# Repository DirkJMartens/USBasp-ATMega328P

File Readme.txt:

My implementation of the USBasp programmer on Windows 10 on a perfboard. 
Changes from the original include: 
  1. using an ATMega328P instead of the original ATMega44/88. 
  2. Changing the input circuit  from using zener diodes to regular diodes 
  3. Omitting the jumper bridges for "Self-programming" and "Slow CLK" 
  4. Power to target is always on. 
Software is using the libusbk driver (signed by Protostack Pty Ltd) and installed using Zadig. 

See project description file for full details.

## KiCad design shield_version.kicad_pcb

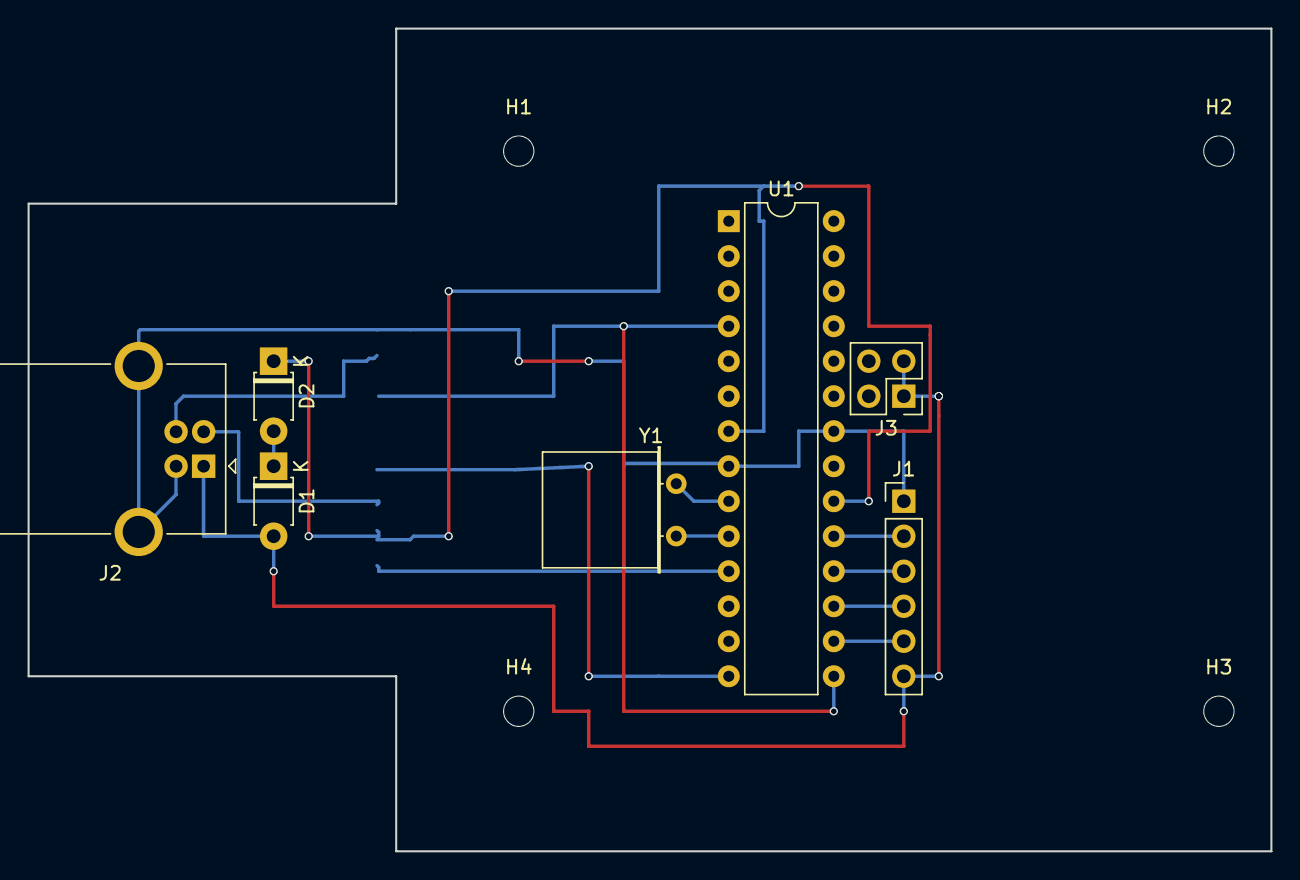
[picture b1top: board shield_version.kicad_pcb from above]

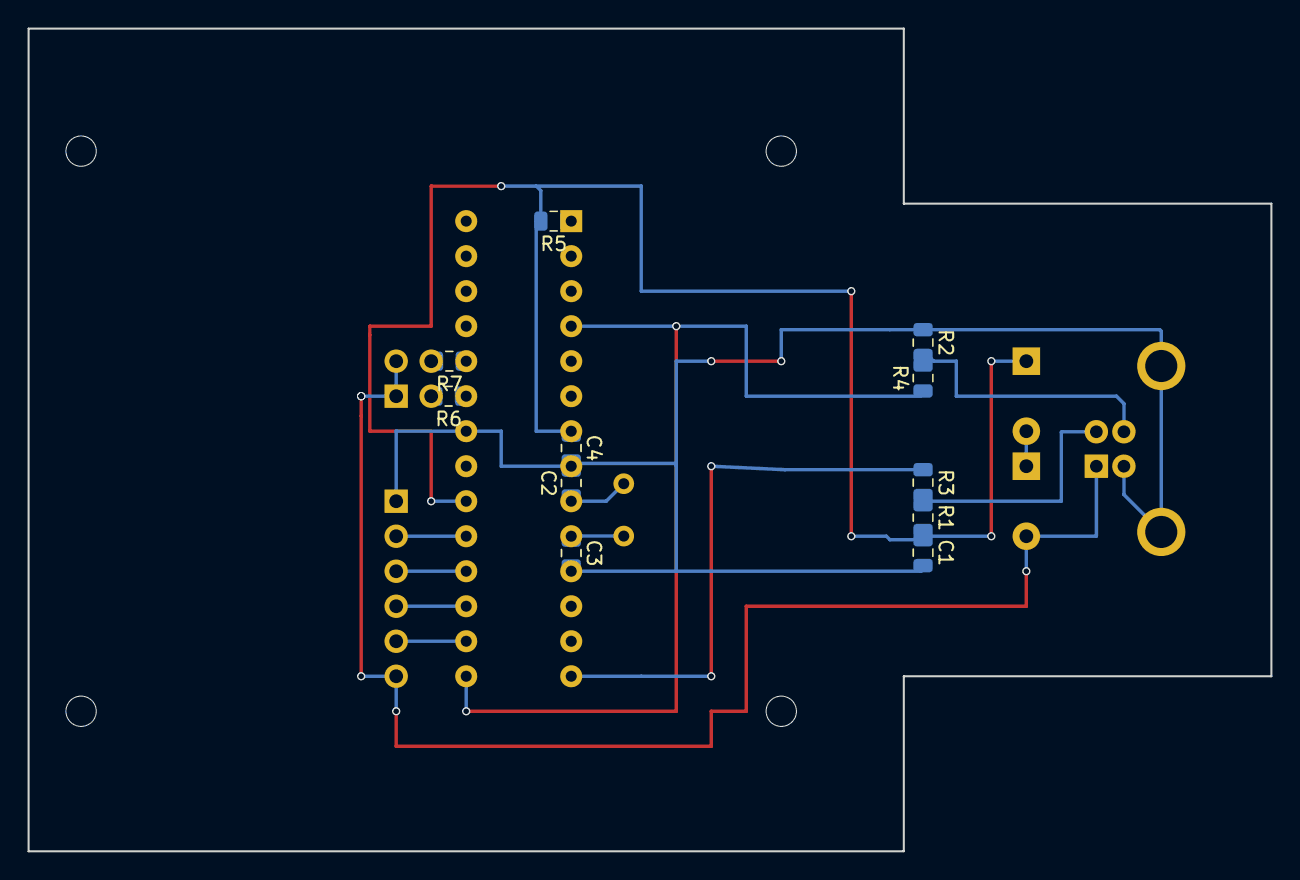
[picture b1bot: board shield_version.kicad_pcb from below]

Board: 2 copper layers, 90.2 x 59.7 mm, 22 parts (11 on the bottom side), 19 nets.

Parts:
C1: 4u7; C_0805_2012Metric
C2, C3: 22p; C_0805_2012Metric
C4: 100n; C_0805_2012Metric
D1, D2: 1N4148; D_T-1_P5.08mm_Horizontal
H1, H2, H3, H4: M3; MountingHole_2.2mm_M2
J1: ICSP6; PinHeader_1x06_P2.54mm_Vertical
J2: USB_B; USB_B_OST_USB-B1HSxx_Horizontal
J3: LEDs; PinHeader_2x02_P2.54mm_Vertical
R1: 1k5; R_0805_2012Metric
R2: 1M; R_0805_2012Metric
R3, R4: 68; R_0805_2012Metric
R5: 10k; R_0805_2012Metric
R6, R7: 1k; R_0805_2012Metric
U1: ATmega328-P; DIP-28_W7.62mm
Y1: 12MHz; Crystal_HC52-8mm_Horizontal

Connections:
+3V3: C1.1, C4.1, D2.1, R1.2, R5.2, U1.7, U1.20
/MISO: J1.3, U1.18
/MOSI: J1.4, U1.17
/SCK: J1.2, U1.19
/~SS: J1.5, U1.16
GND: C1.2, C2.2, C3.2, C4.2, J1.1, J2.4, J2.5, R2.1, U1.8, U1.11, U1.22
unnamed: C2.1, U1.9, Y1.1
unnamed: C3.1, U1.10, Y1.2
unnamed: D1.1, D2.2
unnamed: J2.2, R1.1, R3.2
unnamed: J2.3, R2.2, R4.2
unnamed: J3.2, R6.2
unnamed: J3.4, R7.2
unnamed: R3.1, U1.14
unnamed: R4.1, U1.4, U1.15
unnamed: R5.1, U1.1
unnamed: R6.1, U1.23
unnamed: R7.1, U1.24
VCC: D1.2, J1.6, J2.1, J3.1, J3.3

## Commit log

2021-02-01 Create Readme.txt
    Project description
